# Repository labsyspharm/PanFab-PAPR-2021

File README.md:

# PanFab-PAPR-2021
Greater Boston Pandemic Fabrication Team Powered Air-Purifying Respirator (PanFab PAPR)

Akshay Kothakonda, Lyla Atta, Deborah Plana, Ferrous Ward, Nicole R. LeBoeuf, Peter K. Sorger, <i>et al </i>. 

Publication: https://www.frontiersin.org/articles/10.3389/fbioe.2021.690905/full

<br />This work is licensed under a <a rel="license" href="http://creativecommons.org/licenses/by-sa/4.0/">Creative Commons Attribution-ShareAlike 4.0 International License</a>.

Creative Commons License

This work is licensed under a Creative Commons Attribution-ShareAlike 4.0 International License.

Creative Commons Attribution-ShareAlike 4.0 International Public License

By exercising the Licensed Rights (defined below), You accept and agree to be bound by the terms and conditions of this Creative Commons Attribution-ShareAlike 4.0 International Public License ("Public License"). To the extent this Public License may be interpreted as a contract, You are granted the Licensed Rights in consideration of Your acceptance of these terms and conditions, and the Licensor grants You such rights in consideration of benefits the Licensor receives from making the Licensed Material available under these terms and conditions.

Section 1 – Definitions.

a.	Adapted Material means material subject to Copyright and Similar Rights that is derived from or based upon the Licensed Material and in which the Licensed Material is translated, altered, arranged, transformed, or otherwise modified in a manner requiring permission under the Copyright and Similar Rights held by the Licensor. For purposes of this Public License, where the Licensed Material is a musical work, performance, or sound recording, Adapted Material is always produced where the Licensed Material is synched in timed relation with a moving image.

b.	Adapter's License means the license You apply to Your Copyright and Similar Rights in Your contributions to Adapted Material in accordance with the terms and conditions of this Public License.

c.	BY-SA Compatible License means a license listed at creativecommons.org/compatiblelicenses, approved by Creative Commons as essentially the equivalent of this Public License.

d.	Copyright and Similar Rights means copyright and/or similar rights closely related to copyright including, without limitation, performance, broadcast, sound recording, and Sui Generis Database Rights, without regard to how the rights are labeled or categorized. For purposes of this Public License, the rights specified in Section 2(b)(1)-(2) are not Copyright and Similar Rights.

e.	Effective Technological Measures means those measures that, in the absence of proper authority, may not be circumvented under laws fulfilling obligations under Article 11 of the WIPO Copyright Treaty adopted on December 20, 1996, and/or similar international agreements.

f.	Exceptions and Limitations means fair use, fair dealing, and/or any other exception or limitation to Copyright and Similar Rights that applies to Your use of the Licensed Material.

g.	License Elements means the license attributes listed in the name of a Creative Commons Public License. The License Elements of this Public License are Attribution and ShareAlike.

h.	Licensed Material means the artistic or literary work, database, or other material to which the Licensor applied this Public License.

i.	Licensed Rights means the rights granted to You subject to the terms and conditions of this Public License, which are limited to all Copyright and Similar Rights that apply to Your use of the Licensed Material and that the Licensor has authority to license.

j.	Licensor means the individual(s) or entity(ies) granting rights under this Public License.

k.	Share means to provide material to the public by any means or process that requires permission under the Licensed Rights, such as reproduction, public display, public performance, distribution, dissemination, communication, or importation, and to make material available to the public including in ways that members of the public may access the material from a place and at a time individually chosen by them.

l.	Sui Generis Database Rights means rights other than copyright resulting from Directive 96/9/EC of the European Parliament and of the Council of 11 March 1996 on the legal protection of databases, as amended and/or succeeded, as well as other essentially equivalent rights anywhere in the world.

m.	You means the individual or entity exercising the Licensed Rights under this Public License. Your has a corresponding meaning.
Section 2 – Scope.

a.	License grant. 

1.	Subject to the terms and conditions of this Public License, the Licensor hereby grants You a worldwide, royalty-free, non-sublicensable, non-exclusive, irrevocable license to exercise the Licensed Rights in the Licensed Material to: 

A.	reproduce and Share the Licensed Material, in whole or in part; and

B.	produce, reproduce, and Share Adapted Material.

2.	Exceptions and Limitations. For the avoidance of doubt, where Exceptions and Limitations apply to Your use, this Public License does not apply, and You do not need to comply with its terms and conditions.

3.	Term. The term of this Public License is specified in Section 6(a).

4.	Media and formats; technical modifications allowed. The Licensor authorizes You to exercise the Licensed Rights in all media and formats whether now known or hereafter created, and to make technical modifications necessary to do so. The Licensor waives and/or agrees not to assert any right or authority to forbid You from making technical modifications necessary to exercise the Licensed Rights, including technical modifications necessary to circumvent Effective Technological Measures. For purposes of this Public License, simply making modifications authorized by this Section 2(a)(4) never produces Adapted Material.

5.	Downstream recipients. 

A.	Offer from the Licensor – Licensed Material. Every recipient of the Licensed Material automatically receives an offer from the Licensor to exercise the Licensed Rights under the terms and conditions of this Public License.

B.	Additional offer from the Licensor – Adapted Material. Every recipient of Adapted Material from You automatically receives an offer from the Licensor to exercise the Licensed Rights in the Adapted Material under the conditions of the Adapter’s License You apply.

C.	No downstream restrictions. You may not offer or impose any additional or different terms or conditions on, or apply any Effective Technological Measures to, the Licensed Material if doing so restricts exercise of the Licensed Rights by any recipient of the Licensed Material.

6.	No endorsement. Nothing in this Public License constitutes or may be construed as permission to assert or imply that You are, or that Your use of the Licensed Material is, connected with, or sponsored, endorsed, or granted official status by, the Licensor or others designated to receive attribution as provided in Section 3(a)(1)(A)(i).

b.	Other rights.

1.	Moral rights, such as the right of integrity, are not licensed under this Public License, nor are publicity, privacy, and/or other similar personality rights; however, to the extent possible, the Licensor waives and/or agrees not to assert any such rights held by the Licensor to the limited extent necessary to allow You to exercise the Licensed Rights, but not otherwise.

2.	Patent and trademark rights are not licensed under this Public License.

3.	To the extent possible, the Licensor waives any right to collect royalties from You for the exercise of the Licensed Rights, whether directly or through a collecting society under any voluntary or waivable statutory or compulsory licensing scheme. In all other cases the Licensor expressly reserves any right to collect such royalties.

Section 3 – License Conditions.

Your exercise of the Licensed Rights is expressly made subject to the following conditions.

a.	Attribution.

1.	If You Share the Licensed Material (including in modified form), You must:

A.	retain the following if it is supplied by the Licensor with the Licensed Material: 

i.	identification of the creator(s) of the Licensed Material and any others designated to receive attribution, in any reasonable manner requested by the Licensor (including by pseudonym if designated);

ii.	a copyright notice;

iii.	a notice that refers to this Public License; 

iv.	a notice that refers to the disclaimer of warranties;

v.	a URI or hyperlink to the Licensed Material to the extent reasonably practicable;

B.	indicate if You modified the Licensed Material and retain an indication of any previous modifications; and

C.	indicate the Licensed Material is licensed under this Public License, and include the text of, or the URI or hyperlink to, this Public License.

2.	You may satisfy the conditions in Section 3(a)(1) in any reasonable manner based on the medium, means, and context in which You Share the Licensed Material. For example, it may be reasonable to satisfy the conditions by providing a URI or hyperlink to a resource that includes the required information.

3.	If requested by the Licensor, You must remove any of the information required by Section 3(a)(1)(A) to the extent reasonably practicable.

b.	ShareAlike. 

In addition to the conditions in Section 3(a), if You Share Adapted Material You produce, the following conditions also apply.

1.	The Adapter’s License You apply must be a Creative Commons license with the same License Elements, this version or later, or a BY-SA Compatible License.

2.	You must include the text of, or the URI or hyperlink to, the Adapter's License You apply. You may satisfy this condition in any reasonable manner based on the medium, means, and context in which You Share Adapted Material.

3.	You may not offer or impose any additional or different terms or conditions on, or apply any Effective Technological Measures to, Adapted Material that restrict exercise of the rights granted under the Adapter's License You apply.

Section 4 – Sui Generis Database Rights.

Where the Licensed Rights include Sui Generis Database Rights that apply to Your use of the Licensed Material:

a.	for the avoidance of doubt, Section 2(a)(1) grants You the right to extract, reuse, reproduce, and Share all or a substantial portion of the contents of the database;

b.	if You include all or a substantial portion of the database contents in a database in which You have Sui Generis Database Rights, then the database in which You have Sui Generis Database Rights (but not its individual contents) is Adapted Material, including for purposes of Section 3(b); and

c.	You must comply with the conditions in Section 3(a) if You Share all or a substantial portion of the contents of the database.

For the avoidance of doubt, this Section 4 supplements and does not replace Your obligations under this Public License where the Licensed Rights include other Copyright and Similar Rights. 

Section 5 – Disclaimer of Warranties and Limitation of Liability.

a.	Unless otherwise separately undertaken by the Licensor, to the extent possible, the Licensor offers the Licensed Material as-is and as-available, and makes no representations or warranties of any kind concerning the Licensed Material, whether express, implied, statutory, or other. This includes, without limitation, warranties of title, merchantability, fitness for a particular purpose, non-infringement, absence of latent or other defects, accuracy, or the presence or absence of errors, whether or not known or discoverable. Where disclaimers of warranties are not allowed in full or in part, this disclaimer may not apply to You.

b.	To the extent possible, in no event will the Licensor be liable to You on any legal theory (including, without limitation, negligence) or otherwise for any direct, special, indirect, incidental, consequential, punitive, exemplary, or other losses, costs, expenses, or damages arising out of this Public License or use of the Licensed Material, even if the Licensor has been advised of the possibility of such losses, costs, expenses, or damages. Where a limitation of liability is not allowed in full or in part, this limitation may not apply to You.

c.	The disclaimer of warranties and limitation of liability provided above shall be interpreted in a manner that, to the extent possible, most closely approximates an absolute disclaimer and waiver of all liability.

Section 6 – Term and Termination.

a.	This Public License applies for the term of the Copyright and Similar Rights licensed here. However, if You fail to comply with this Public License, then Your rights under this Public License terminate automatically.

b.	Where Your right to use the Licensed Material has terminated under Section 6(a), it reinstates:

1.	automatically as of the date the violation is cured, provided it is cured within 30 days of Your discovery of the violation; or

2.	upon express reinstatement by the Licensor.

For the avoidance of doubt, this Section 6(b) does not affect any right the Licensor may have to seek remedies for Your violations of this Public License.

c.	For the avoidance of doubt, the Licensor may also offer the Licensed Material under separate terms or conditions or stop distributing the Licensed Material at any time; however, doing so will not terminate this Public License.

d.	Sections 1, 5, 6, 7, and 8 survive termination of this Public License.

Section 7 – Other Terms and Conditions.

a.	The Licensor shall not be bound by any additional or different terms or conditions communicated by You unless expressly agreed.

b.	Any arrangements, understandings, or agreements regarding the Licensed Material not stated herein are separate from and independent of the terms and conditions of this Public License.

Section 8 – Interpretation.

a.	For the avoidance of doubt, this Public License does not, and shall not be interpreted to, reduce, limit, restrict, or impose conditions on any use of the Licensed Material that could lawfully be made without permission under this Public License.

b.	To the extent possible, if any provision of this Public License is deemed unenforceable, it shall be automatically reformed to the minimum extent necessary to make it enforceable. If the provision cannot be reformed, it shall be severed from this Public License without affecting the enforceability of the remaining terms and conditions.

c.	No term or condition of this Public License will be waived and no failure to comply consented to unless expressly agreed to by the Licensor.

d.	Nothing in this Public License constitutes or may be interpreted as a limitation upon, or waiver of, any privileges and immunities that apply to the Licensor or You, including from the legal processes of any jurisdiction or authority.

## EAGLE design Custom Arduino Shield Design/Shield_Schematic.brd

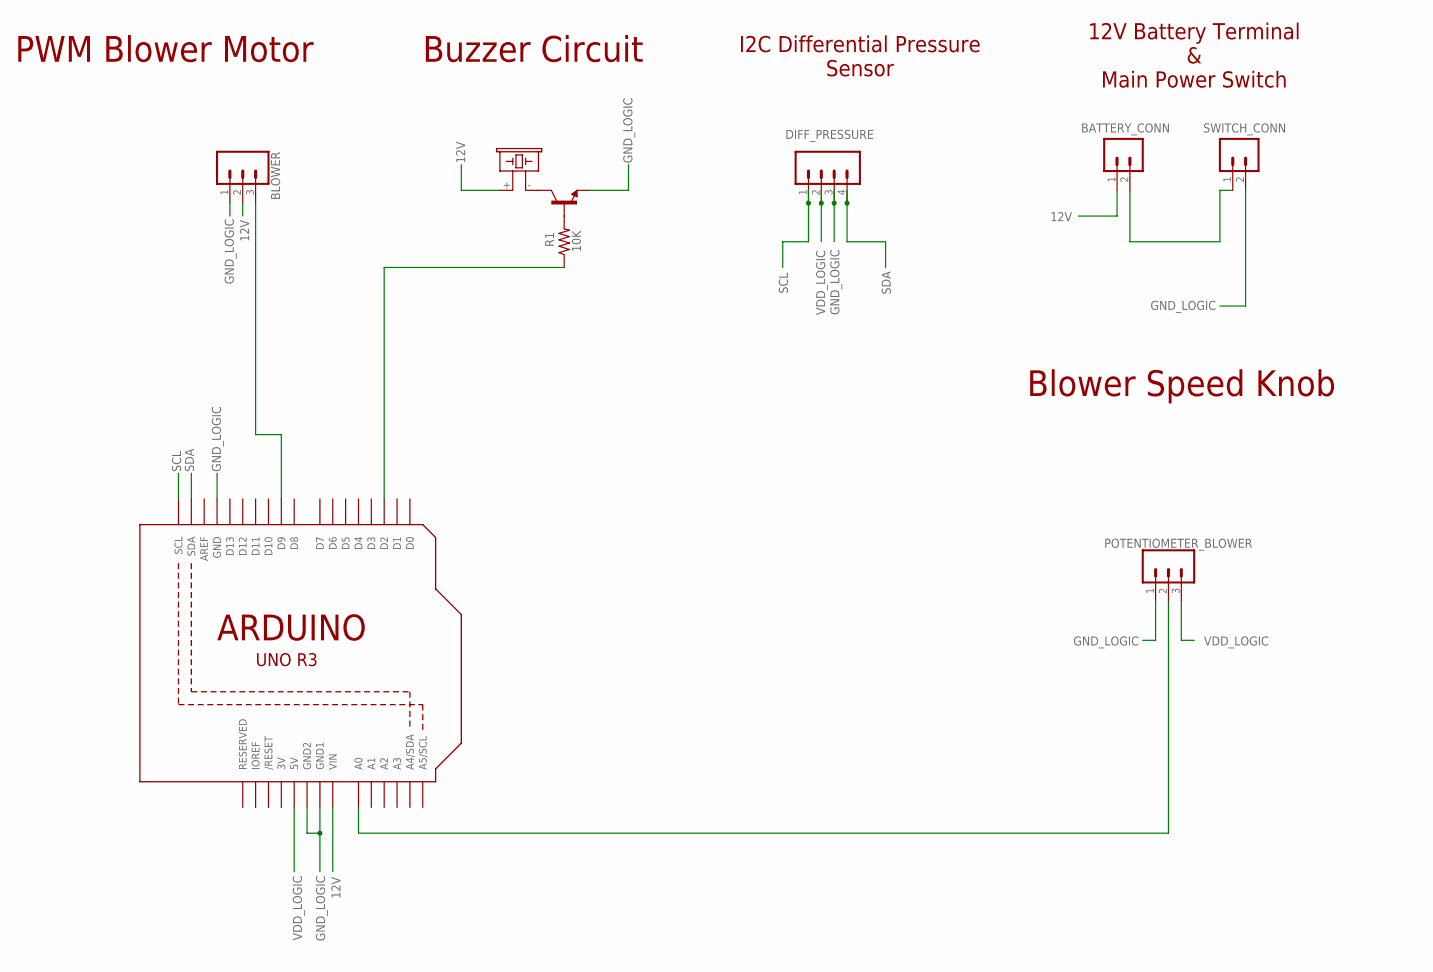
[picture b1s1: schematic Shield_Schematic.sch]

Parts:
BATTERY_CONN: CONN_02PTH4; 1X02_XTRA_BIG
BLOWER: CONN_03; 1X03
DIFF_PRESSURE: CONN_04; 1X04
POTENTIOMETER_BLOWER: CONN_03; 1X03
R1: 10K; P0817V
SG1: F/CM12P
SWITCH_CONN: CONN_02PTH4; 1X02_XTRA_BIG
T1: 2N5089; TO92
U1: ARDUINOR3-DIMENSION; ARDUINOR3

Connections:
3V: U1.3V
12V: BATTERY_CONN.1, BLOWER.2, SG1.+ (1), U1.VIN
GND_LOGIC: BLOWER.1, DIFF_PRESSURE.3, POTENTIOMETER_BLOWER.1, SWITCH_CONN.2, T1.3 (E), U1.GND, U1.GND1, U1.GND2
unnamed: POTENTIOMETER_BLOWER.2, U1.A0
unnamed: BLOWER.3, U1.D9
unnamed: R1.1, U1.D2
unnamed: R1.2, T1.2 (B)
unnamed: SG1.- (2), T1.1 (C)
unnamed: BATTERY_CONN.2, SWITCH_CONN.1
SCL: DIFF_PRESSURE.1, U1.SCL
SDA: DIFF_PRESSURE.4, U1.SDA
VDD_LOGIC: DIFF_PRESSURE.2, POTENTIOMETER_BLOWER.3, U1.5V

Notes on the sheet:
PWM Blower Motor
Buzzer Circuit
I2C Differential Pressure Sensor
12V Battery Terminal & Main Power Switch
Blower Speed Knob

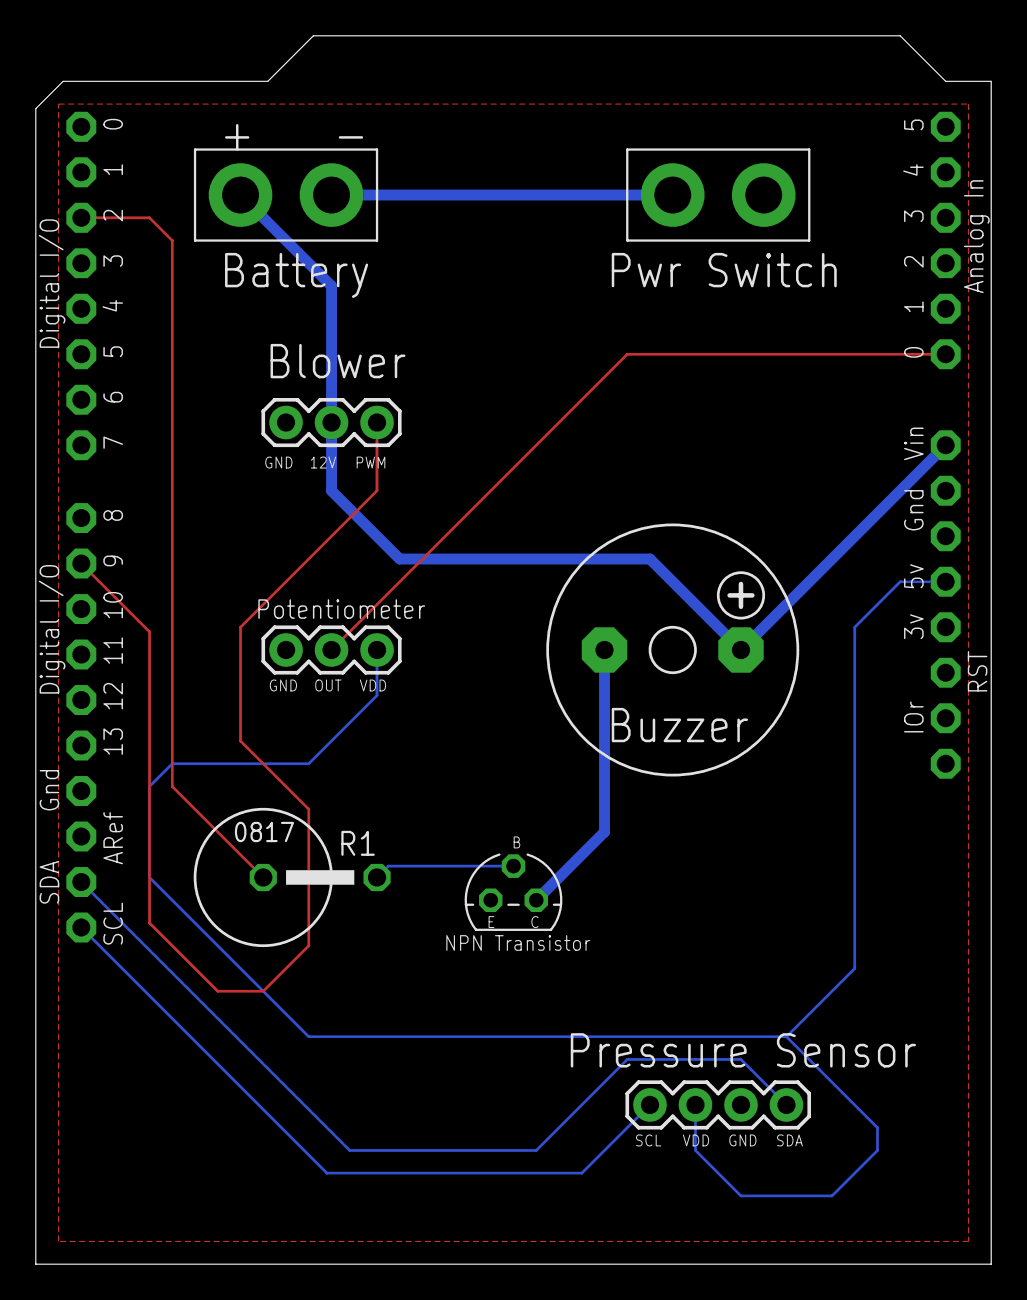
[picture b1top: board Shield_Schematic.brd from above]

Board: 2 copper layers, 53.3 x 68.6 mm, 9 parts (0 on the bottom side), 11 nets.

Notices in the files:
parts and their libraries:
SparkFun-Connectors: Licensing: Creative Commons ShareAlike 4.0 International - https://creativecommons.org/licenses/by-sa/4.0
